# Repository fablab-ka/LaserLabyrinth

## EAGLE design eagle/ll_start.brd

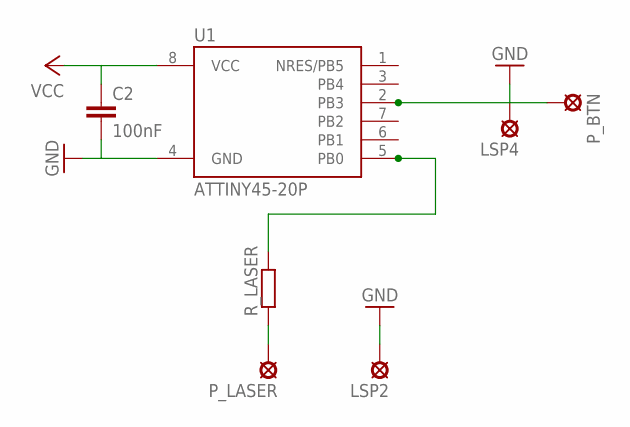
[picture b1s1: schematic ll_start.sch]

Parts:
C2: 100nF; C025-025X050
LSP2, LSP4: LSP10
P_BTN: LSP10
P_LASER: LSP10
R_LASER: R-EU_0204/7; 0204/7
U1: ATTINY45-20P; PDIP08_300MIL

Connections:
GND: C2.2, LSP2.MP, LSP4.MP, U1.4 (GND)
MOSI: R_LASER.2, U1.5 (PB0)
unnamed: P_LASER.MP, R_LASER.1
unnamed: P_BTN.MP, U1.2 (PB3)
VCC: C2.1, U1.8 (VCC)

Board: 2 copper layers, 7 parts (0 on the bottom side), 5 nets, no tracks yet.

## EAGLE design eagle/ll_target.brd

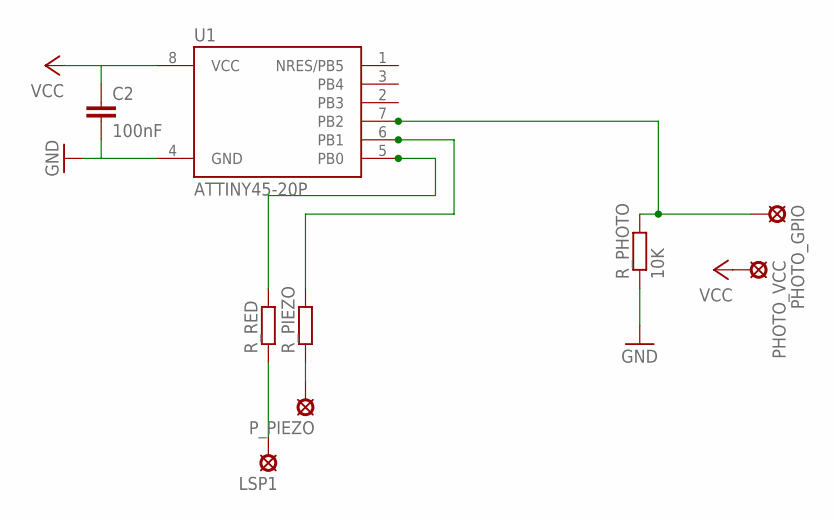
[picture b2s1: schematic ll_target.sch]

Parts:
C2: 100nF; C025-025X050
LSP1: LSP10
PHOTO_GPIO: LSP10
PHOTO_VCC: LSP10
P_PIEZO: LSP10
R_PHOTO: 10K; 0204/7
R_PIEZO: R-EU_0204/7; 0204/7
R_RED: R-EU_0204/7; 0204/7
U1: ATTINY45-20P; PDIP08_300MIL

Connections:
GND: C2.2, R_PHOTO.1, U1.4 (GND)
MISO: R_PIEZO.2, U1.6 (PB1)
MOSI: R_RED.2, U1.5 (PB0)
unnamed: P_PIEZO.MP, R_PIEZO.1
unnamed: LSP1.MP, R_RED.1
SCK: PHOTO_GPIO.MP, R_PHOTO.2, U1.7 (PB2)
VCC: C2.1, PHOTO_VCC.MP, U1.8 (VCC)

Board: 2 copper layers, 9 parts (0 on the bottom side), 7 nets, no tracks yet.

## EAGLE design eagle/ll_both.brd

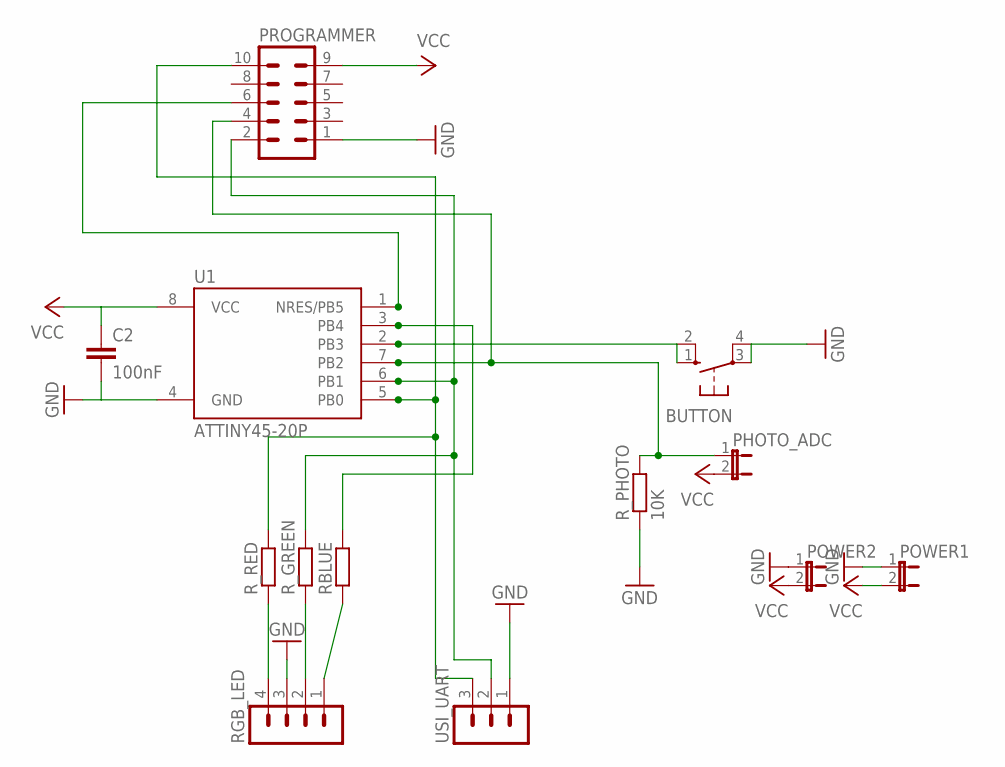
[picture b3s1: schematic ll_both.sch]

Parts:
BUTTON: 10-XX; B3F-10XX
C2: 100nF; C025-025X050
PHOTO_ADC: JP1E; JP1
POWER1, POWER2: JP1E; JP1
PROGRAMMER: MA05-2
RBLUE: R-EU_0204/7; 0204/7
RGB_LED: MA04-1
R_GREEN: R-EU_0204/7; 0204/7
R_PHOTO: 10K; 0204/7
R_RED: R-EU_0204/7; 0204/7
U1: ATTINY45-20P; PDIP08_300MIL
USI_UART: MA03-1

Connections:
GND: BUTTON.3, BUTTON.4 (P1), C2.2, POWER1.1, POWER2.1, PROGRAMMER.1, RGB_LED.3, R_PHOTO.1, U1.4 (GND), USI_UART.1
MISO: PROGRAMMER.2, R_GREEN.2, U1.6 (PB1), USI_UART.2
MOSI: PROGRAMMER.10, R_RED.2, U1.5 (PB0), USI_UART.3
unnamed: RGB_LED.2, R_GREEN.1
unnamed: RGB_LED.4, R_RED.1
unnamed: RBLUE.2, U1.3 (PB4)
unnamed: RBLUE.1, RGB_LED.1
unnamed: BUTTON.1 (S), BUTTON.2 (S1), U1.2 (PB3)
RESET: PROGRAMMER.6, U1.1 (NRES/PB5)
SCK: PHOTO_ADC.1, PROGRAMMER.4, R_PHOTO.2, U1.7 (PB2)
VCC: C2.1, PHOTO_ADC.2, POWER1.2, POWER2.2, PROGRAMMER.9, U1.8 (VCC)

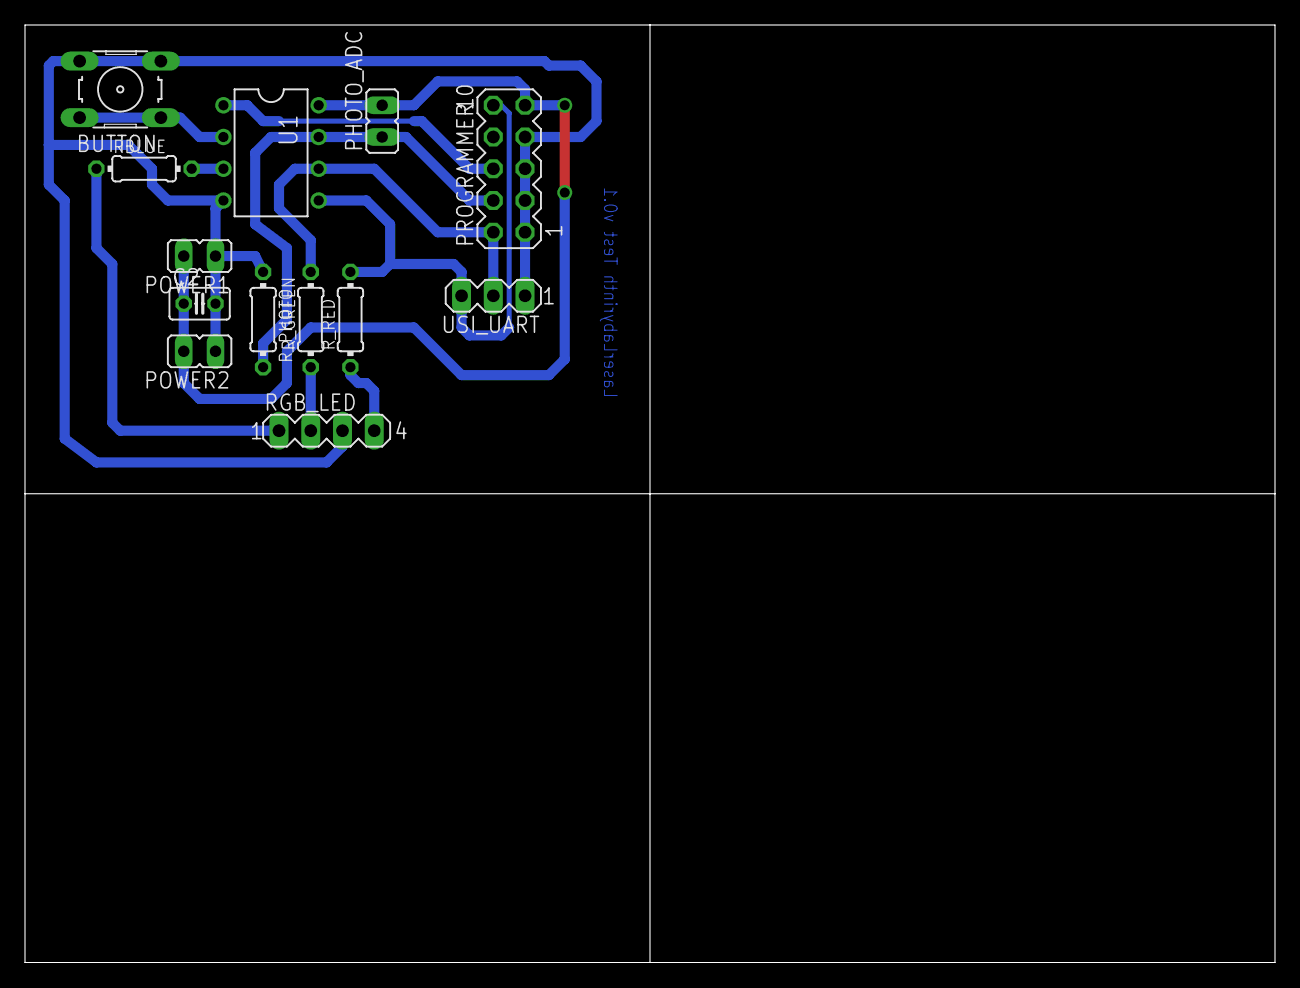
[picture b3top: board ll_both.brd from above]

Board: 2 copper layers, 100.0 x 75.0 mm, 13 parts (0 on the bottom side), 11 nets.

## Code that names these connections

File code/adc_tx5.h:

/*
 * adc.h
 *
 *  Created on: Mar 2, 2017
 *      Author: Mark Weinreuter
 */

#ifndef ADC_ADC_H_
#define ADC_ADC_H_

#include <avr/io.h>
#include "common.h"

#if  defined (__AVR_ATtiny25__) || defined (__AVR_ATtiny45__) || defined (__AVR_ATtiny85__)

/**
 * Turn on power reduction. ADC must be disabled!
 * NOTE: cannot use ACD MUX as AC input.
 */
#define adc_power_reduction_off()           PRR &= ~bit(PRADC)
#define adc_power_reduction_on()            PRR |= bit(PRADC)

#define ADC_VALUE_LOW                        ADCL
#define ADC_VALUE_HIGH                        ADCH
#define ADC_VALUE_16_BIT                    ADCW/* 10bits are used*/
#define ADC_COMPLETE_INTERRUPT_FLAG            ADIF

#define AREF_PIN                            PB0

#define ADC_MUX_0_PIN                       PB0
#define ADC_MUX_1_PIN                       PB1
#define ADC_MUX_2_PIN                       PB2
#define ADC_MUX_3_PIN                       PB3
/** Note: this is also the I2c-SDA-pin */
#define ADC_MUX_4_PIN                       PB4
/** Note: this is also the I2c-SCL-pin */
#define ADC_MUX_5_PIN                       PB5

#define adc_clearReferenceBits()                ADMUX &= ~bit3(REFS0, REFS1, REFS2)
#define adc_setReferenceVCC()                    adc_clearReferenceBits()
#define adc_setReferenceAREF()                    adc_clearReferenceBits(); ADMUX |= bit(REFS0)
#define adc_setReferenceInternal_1_1V()            adc_clearReferenceBits(); ADMUX |= bit2(       REFS1)
#define adc_setReferenceInternal_2_56V()        adc_clearReferenceBits(); ADMUX |= bit2(       REFS1, REFS2)
#define adc_setReferenceInternal_2_56V_Cap()                              ADMUX |= bit3(REFS0, REFS1, REFS2)

/**
 * Uses the bits 0,1 of ADCH and all of ADCL.
 */
#define adc_useRightAlignedData()            ADMUX &= ~bit(ADLAR)

/**
 * Uses all bits ADCH and 7,6 of ADCL.
 */
#define adc_useLeftAlignedData()            ADMUX |= bit(ADLAR)

/**
 * Ensures, that the values are clamped to 2^range possible values)
 */
#define adc_valuesInRange(adcValue, range)            (adcValue >> (10 -range))

//specifies which of the 0-7 pins to use for the adc input
#define adc_clearMuxBits()                    ADMUX &= ~bit4(MUX3, MUX2,  MUX1, MUX0)
#define adc_useADC_0()                        adc_clearMuxBits()
#define adc_useADC_1()                        adc_clearMuxBits(); ADMUX |= bit(MUX0)
#define adc_useADC_2()                        adc_clearMuxBits(); ADMUX |=        bit(MUX1)
#define adc_useADC_3()                        adc_clearMuxBits(); ADMUX |= bit2(MUX0, MUX1)
/*
 * TODO:
#define adc_useADC_6()						adc_clearMuxBits(); ADMUX |= bit2(MUX1, MUX2)
#define adc_useADC_7()						adc_clearMuxBits(); ADMUX |= bit3(MUX0, MUX1, MUX2)
#define adc_use_1_1V()						adc_clearMuxBits(); ADMUX |= bit3(MUX1, MUX2, MUX3)
#define adc_useGND()						adc_clearMuxBits(); ADMUX |= bit4(MUX0, MUX1, MUX2, MUX3)

*/


/**
 * Enables the adc.
 */
#define adc_enable()                        ADCSRA |= bit(ADEN)
/**
 * Disables the adc and terminates a pending conversion.
 */
#define adc_disable()                        ADCSRA &= ~bit(ADEN)

/**
 * Start a conversion.
 */
#define adc_start()                            ADCSRA |= bit(ADSC)

//wait till the bit is cleared
#define adc_waitForConversionComplete()        while(ADCSRA & bit(ADSC))

#define adc_enableAutoTriggerMode()            ADCSRA |= bit(ADATE)

#define adc_enableCompleteInterrupt()        ADCSRA |= bit(ADIE)

//first clears the unused bits and sets the required ones => enables easy switching
#define adc_clearPrescalerBits()            ADCSRA = (ADCSRA & ~bit3(ADPS0, ADPS1, ADPS2))
#define adc_prescalerOff()                    adc_clearPrescalerBits();
#define adc_prescaler2()                    adc_clearPrescalerBits();        ADCSRA |= bit(ADPS0)
#define adc_prescaler4()                    adc_clearPrescalerBits();        ADCSRA |= bit(ADPS1)
#define adc_prescaler8()                    adc_clearPrescalerBits();        ADCSRA |= bit2(ADPS0, ADPS1)
#define adc_prescaler16()                    adc_clearPrescalerBits();        ADCSRA |= bit(ADPS2)
#define adc_prescaler32()                    adc_clearPrescalerBits();        ADCSRA |= bit2(ADPS0, ADPS2)
#define adc_prescaler64()                    adc_clearPrescalerBits();        ADCSRA |= bit2(ADPS1, ADPS2)
#define adc_prescaler128()                                                     ADCSRA |= bit3(ADPS0, ADPS1, ADPS2)

//disables the specified adc, should be used to reduce power consumption
//if an analog signal is applied at ADC0...5
#define adc_disableADC_0()                    DIDR0 |= bit(ADC0D)
#define adc_disableADC_1()                    DIDR0 |= bit(ADC1D)
#define adc_disableADC_2()                    DIDR0 |= bit(ADC2D)
#define adc_disableADC_3()                    DIDR0 |= bit(ADC3D)

//if ADATE is set, these select the trigger source for an ADC conversion
//see the data sheet for some more information about interupts and switching modes
#define adc_autoTriggerFreeRunning()                ADCSRB = (ADCSRB & ~(1 << ADTS0 | 1 <<  ADTS1 | 1 << ADTS2))
#define adc_autoTriggerAnalogComp()                ADCSRB = (ADCSRB & ~(              1 <<  ADTS1 | 1 << ADTS2)) | (1 << ADTS0)
#define adc_autoTriggerExtInterrupt0()            ADCSRB = (ADCSRB & ~(1 << ADTS0              | 1 << ADTS2)) | (             1 << ADTS1)
// TODO: add more!


#else
#error "Chip not yet supported."
#endif


extern unsigned int adc_getSampleBlocking(byte samples);

#endif /* ADC_ADC_H_ */

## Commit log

2017-02-23 python script to generate svgs files for the gameboard/grid.
2017-02-23 Added hexagonal grid since it is way cooler
2017-02-24 Added drawing to determine mirror positions.
2017-02-24 Make a hexagonal grid with roughly 4cm block sizes.
2017-02-24 block with connector holes. Dunno if this is a good idea yet.
2017-03-01 Removed regular grid files. The gameboard will be a hex grid.
2017-03-01 Testing base slid design. Added Dummy mirror holder.
2017-03-02 Added mirror connector 3d file for a test mirror.
2017-03-07 Initial avr code for an attiny45 chip.
2017-03-07 Eagle files for a simple test board
2017-03-13 first eagle pcb layout
2017-03-13 pulse laser and reconstruct via adc.
2017-03-13 new models and some testing needs cleanup
2017-03-13 initial laser start design.
2017-03-30 Added svg files for laser cutting the hex blocks.
2017-04-02 changed laser start code.
2017-04-04 new parts for beam splitter and placeholder.
2017-04-05 Added 3d preview of the board :)
2017-04-06 Aufräumen.
2017-04-11 new files...
2017-04-12 working on doku.
2017-04-19 battery box lid corrections.
2017-04-19 Cleanup.
2017-04-21 move svgs in one file.
2017-05-02 changes to the grid.
2017-06-06 batch commit...
